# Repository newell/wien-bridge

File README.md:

# Wien Bridge Oscillator

A Wien bridge oscillator is an electronic oscillator circuit that is used to generate sinusoidal waveforms at a specific frequency. It is named after its inventor Max Wien. The oscillator uses a combination of resistors, capacitors, and an operational amplifier (op-amp) to create a feedback network that sustains the oscillations.

The basic configuration of a Wien bridge oscillator consists of an op-amp with positive feedback, along with a bridge network composed of resistors and capacitors. The bridge network is typically configured as a series combination of a resistor ($R$) and a capacitor ($C$) in one branch, and two resistors ($R$) in the other branch. The output of the op-amp is fed back to the bridge network through a voltage divider network.

The operation of the Wien bridge oscillator is based on the concept of the bridge network producing a phase shift of 180 degrees at the desired oscillation frequency. By adjusting the values of the resistors and capacitors in the bridge network, the frequency of oscillation can be set. The feedback provided by the bridge network ensures that the op-amp output maintains the required phase and amplitude to sustain the oscillations.

One of the key features of the Wien bridge oscillator is its ability to produce a sinusoidal waveform with good frequency stability and low distortion. It achieves this by maintaining the feedback network in balance, where the gain and phase shift around the loop are precisely controlled.

The frequency of oscillation in a Wien bridge oscillator is given by the formula:

$$\begin{align}f = \frac{1}{2\pi RC}\end{align}$$

where $R$ and $C$ are the values of the resistors and capacitors in the bridge network. By adjusting these values, the oscillation frequency can be tuned.

Wien bridge oscillators find applications in various areas such as audio signal generation, frequency synthesis, and test equipment. They provide a simple and reliable means of generating sinusoidal waveforms with good frequency accuracy and low distortion.

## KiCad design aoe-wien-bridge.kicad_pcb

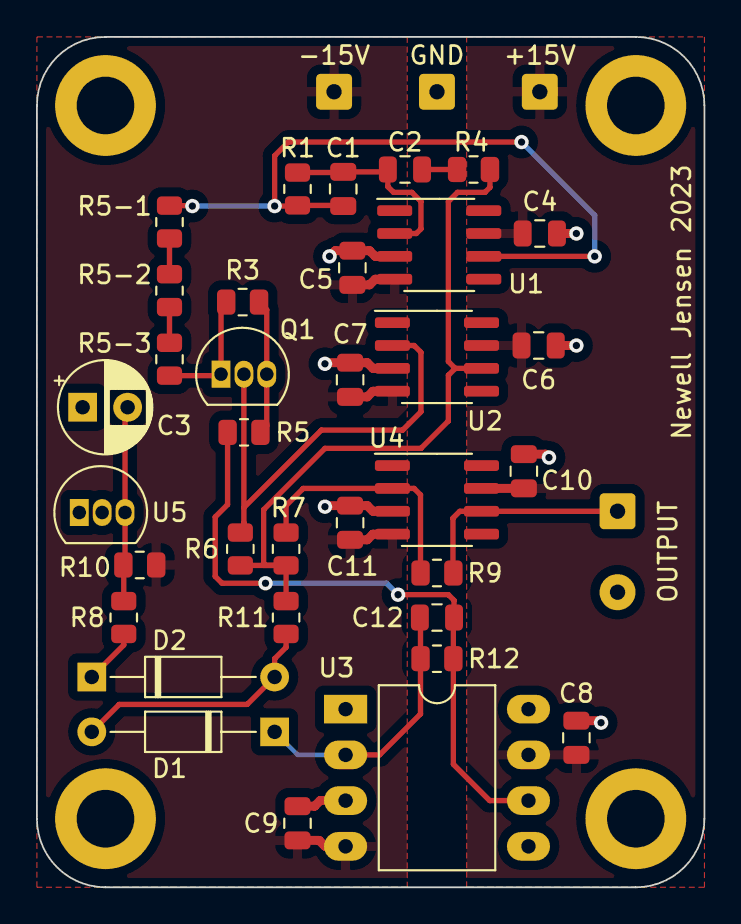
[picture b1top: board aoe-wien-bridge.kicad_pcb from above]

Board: 2 copper layers, 37.1 x 47.2 mm, 38 parts (0 on the bottom side), 19 nets.

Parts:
+15V: Conn_01x01; SolderWire-0.25sqmm_1x01_D0.65mm_OD2mm
-15V: Conn_01x01; SolderWire-0.25sqmm_1x01_D0.65mm_OD2mm
C1, C2: 10nF (film); C_0805_2012Metric
C3: 10uF; CP_Radial_D5.0mm_P2.50mm
C4, C5, C6, C7, C8, C9, C10, C11, C12: 100nF; C_0805_2012Metric
D1, D2: 1N5711; D_DO-35_SOD27_P10.16mm_Horizontal
GND: Conn_01x01; SolderWire-0.25sqmm_1x01_D0.65mm_OD2mm
OUTPUT: Conn_Coaxial; SolderWire-0.25sqmm_1x02_P4.5mm_D0.65mm_OD2mm
Q1: J111; TO-92L_Inline
R1, R4, R5-1: *15.0k; R_0805_2012Metric
R3, R5: *1M; R_0805_2012Metric
R5-2: *4.42k; R_0805_2012Metric
R5-3: *4.02k; R_0805_2012Metric
R6: *40.2k; R_0805_2012Metric
R7: *10k; R_0805_2012Metric
R8: 49.9k; R_0805_2012Metric
R9: *49.9k; R_0805_2012Metric
R10: 10k; R_0805_2012Metric
R11: 18.7k; R_0805_2012Metric
R12: 22M; R_0805_2012Metric
U1, U2, U4: OPA627; SOIC-8_3.9x4.9mm_P1.27mm
U3: LF411; DIP-8_W10.16mm_LongPads
U5: LM336-5; TO-92L_Inline

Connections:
+15V: +15V.1, C4.1, C6.1, C8.1, C10.1, U1.7, U2.7, U3.7, U4.7
-15V: -15V.1, C5.1, C7.1, C9.1, C11.1, R10.2, U1.4, U2.4, U3.4, U4.4
GNDREF: C3.1, C4.2, C5.2, C6.2, C7.2, C8.2, C9.2, C10.2, C11.2, GND.1, OUTPUT.2 (Ext), U1.3 (+), U2.3 (+), U3.3 (+), U4.3 (+), U5.2 (K)
unnamed: C1.1, C2.1, R1.1, U1.2 (-)
unnamed: C1.2, R1.2, R5-1.1, U1.6
unnamed: C2.2, R4.1
unnamed: C3.2, R8.2, R10.1, U5.3 (A)
unnamed: C12.1, R5.2, R12.1, U3.6
unnamed: C12.2, D1.1 (K), R12.2, U3.2 (-)
unnamed: D1.2 (A), D2.2 (A), R11.1
unnamed: D2.1 (K), R8.1
unnamed: OUTPUT.1 (In), R9.2, U4.6
unnamed: Q1.1 (D), R3.1, R5-3.2
unnamed: Q1.2 (S), R6.1, U2.2 (-)
unnamed: Q1.3 (G), R3.2, R5.1
unnamed: R5-1.2, R5-2.1
unnamed: R5-2.2, R5-3.1
unnamed: R7.2, R9.1, U4.2 (-)
unnamed: R4.2, R6.2, R7.1, R11.2, U2.6

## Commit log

2023-06-27 Add datasheets
2023-06-27 Add schematic
2023-06-27 Add pcb
